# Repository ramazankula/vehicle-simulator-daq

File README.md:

# vehicle-simulator-daq
##Vehicle Simulator Data Acquisition Board

This project collects all simulator data and sends them to the simulation software using USB port.

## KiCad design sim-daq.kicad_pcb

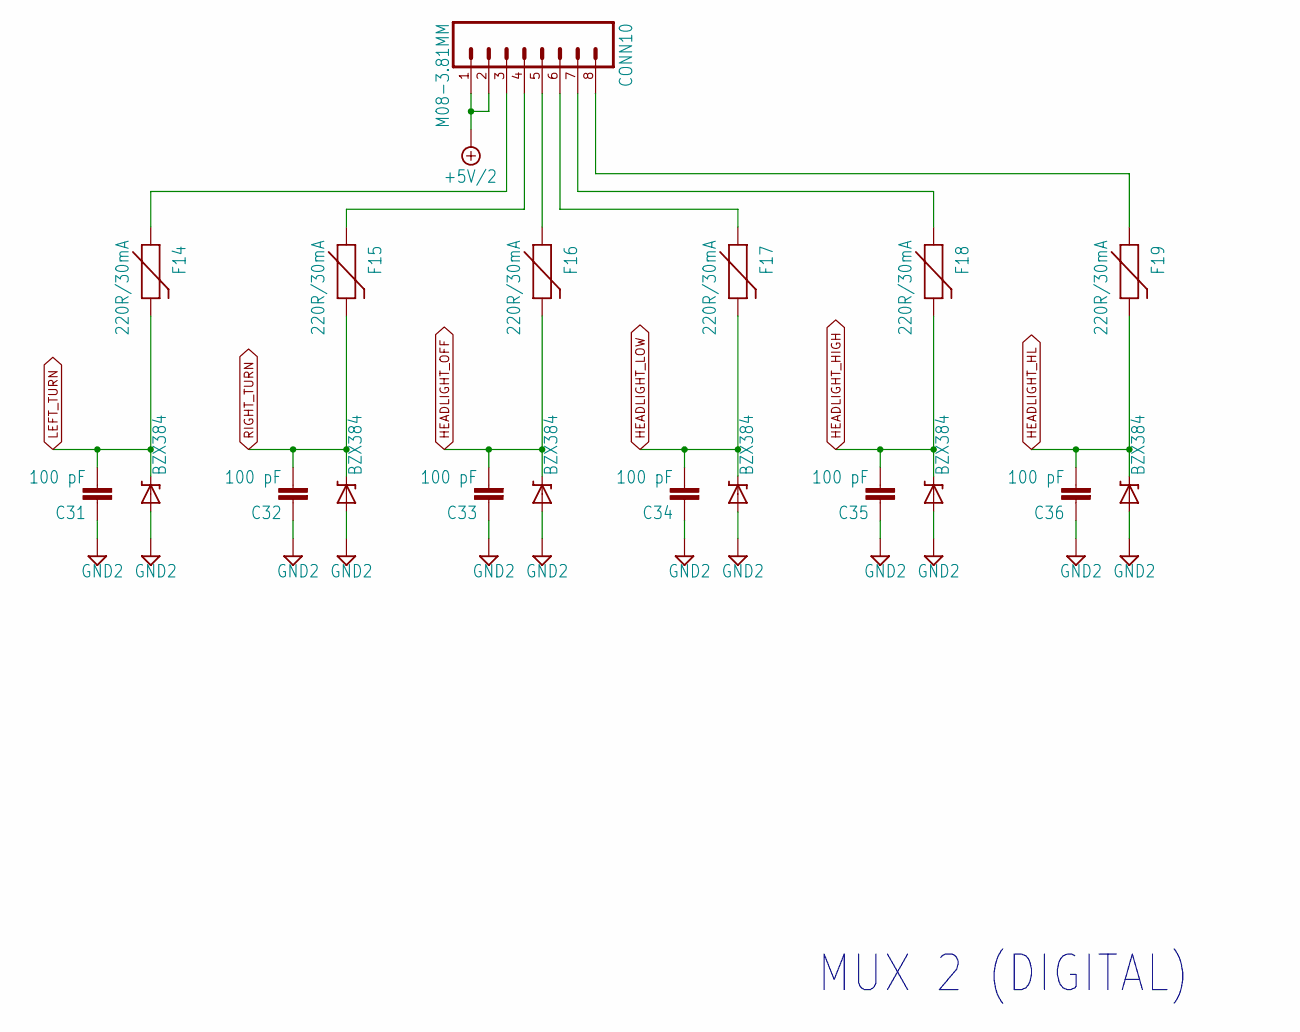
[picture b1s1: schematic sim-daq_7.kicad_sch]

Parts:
C31, C32, C33, C34, C35, C36: 100 pF; C0805; PARTNO *
CONN10: M08-3.81MM; M08-3.81; PARTNO *
D33, D34, D35, D36, D37, D38: BZX384; SOD-323; PARTNO *
F14, F15, F16, F17, F18, F19: 220R/30mA; 0603; PARTNO *

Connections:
+5V/2: CONN10.1, CONN10.2; also elsewhere on the board
GND2: C31.1, C32.1, C33.1, C34.1, C35.1, C36.1, D33.A, D34.A, D35.A, D36.A, D37.A, D38.A; also elsewhere on the board
HEADLIGHT_HIGH: C35.2, D37.C, F18.2; also elsewhere on the board
HEADLIGHT_HL: C36.2, D38.C, F19.2; also elsewhere on the board
HEADLIGHT_LOW: C34.2, D36.C, F17.2; also elsewhere on the board
HEADLIGHT_OFF: C33.2, D35.C, F16.2; also elsewhere on the board
LEFT_TURN: C31.2, D33.C, F14.2; also elsewhere on the board
unnamed: CONN10.3, F14.1
unnamed: CONN10.4, F15.1
unnamed: CONN10.5, F16.1
unnamed: CONN10.6, F17.1
unnamed: CONN10.7, F18.1
unnamed: CONN10.8, F19.1
RIGHT_TURN: C32.2, D34.C, F15.2; also elsewhere on the board

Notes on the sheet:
MUX 2 (DIGITAL)

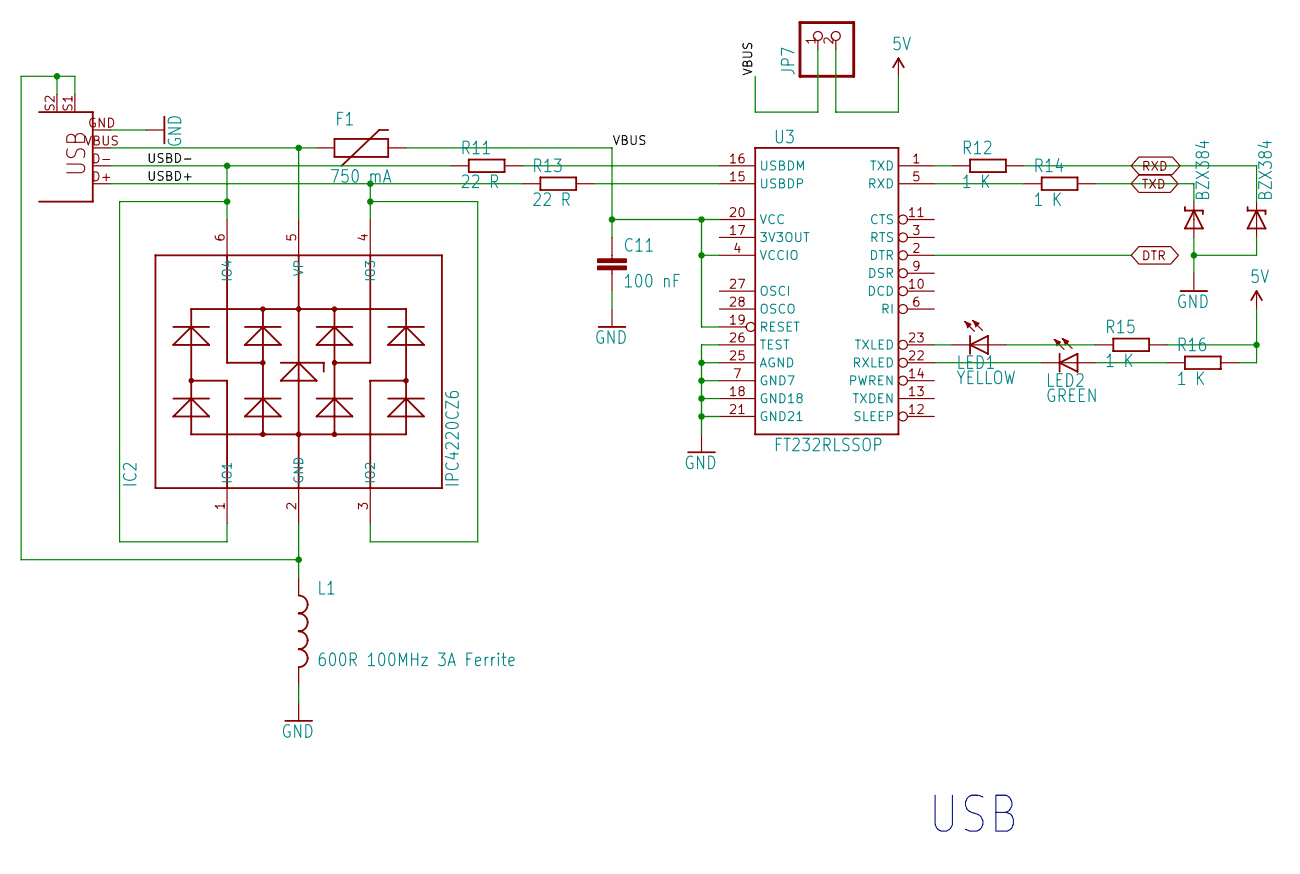
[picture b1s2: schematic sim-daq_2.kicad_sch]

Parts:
C11: 100 nF; C0805; PARTNO *
CONN2: USB+SHIELD; USB-B-PTH; PARTNO *
D14, D15: BZX384; SOD-323; PARTNO *
F1: 750 mA; PTC-1206-WIDE; PARTNO *
IC2: IPC4220CZ6; TSOP-6; PARTNO *
JP7: PINHD-1X2; 1X02; PARTNO *
L1: 600R 100MHz 3A Ferrite; 1210; PARTNO *
LED1: YELLOW; CHIPLED_0805; PARTNO *
LED2: GREEN; CHIPLED_0805; PARTNO *
R11, R13: 22 R; R0805; PARTNO *
R12, R14, R15, R16: 1 K; R0805; PARTNO *
U3: FT232RLSSOP; SSOP28DB; PARTNO *

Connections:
5V: JP7.2, R15.2, R16.2; also elsewhere on the board
/sim-daq_2/USBD+: CONN2.D+, IC2.3 (IO2), IC2.4 (IO3), R13.1
/sim-daq_2/USBD-: CONN2.D-, IC2.1 (IO1), IC2.6 (IO4), R11.1
/sim-daq_2/VBUS: C11.1, F1.2, JP7.1, U3.4 (VCCIO), U3.19 (RESET), U3.20 (VCC)
DTR: U3.2 (DTR); also elsewhere on the board
GND: C11.2, CONN2.GND, D14.A, D15.A, L1.2, U3.7 (GND7), U3.18 (GND18), U3.21 (GND21), U3.25 (AGND), U3.26 (TEST); also elsewhere on the board
unnamed: CONN2.S1, CONN2.S2, IC2.2 (GND), L1.1
unnamed: CONN2.VBUS, F1.1, IC2.5 (VP)
unnamed: LED1.A, R15.1
unnamed: LED2.A, R16.1
unnamed: R14.1, U3.5 (RXD)
unnamed: LED2.C, U3.22 (RXLED)
unnamed: R12.1, U3.1 (TXD)
unnamed: LED1.C, U3.23 (TXLED)
unnamed: R11.2, U3.16 (USBDM)
unnamed: R13.2, U3.15 (USBDP)
RXD: D15.C, R12.2; also elsewhere on the board
TXD: D14.C, R14.2; also elsewhere on the board

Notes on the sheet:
USB

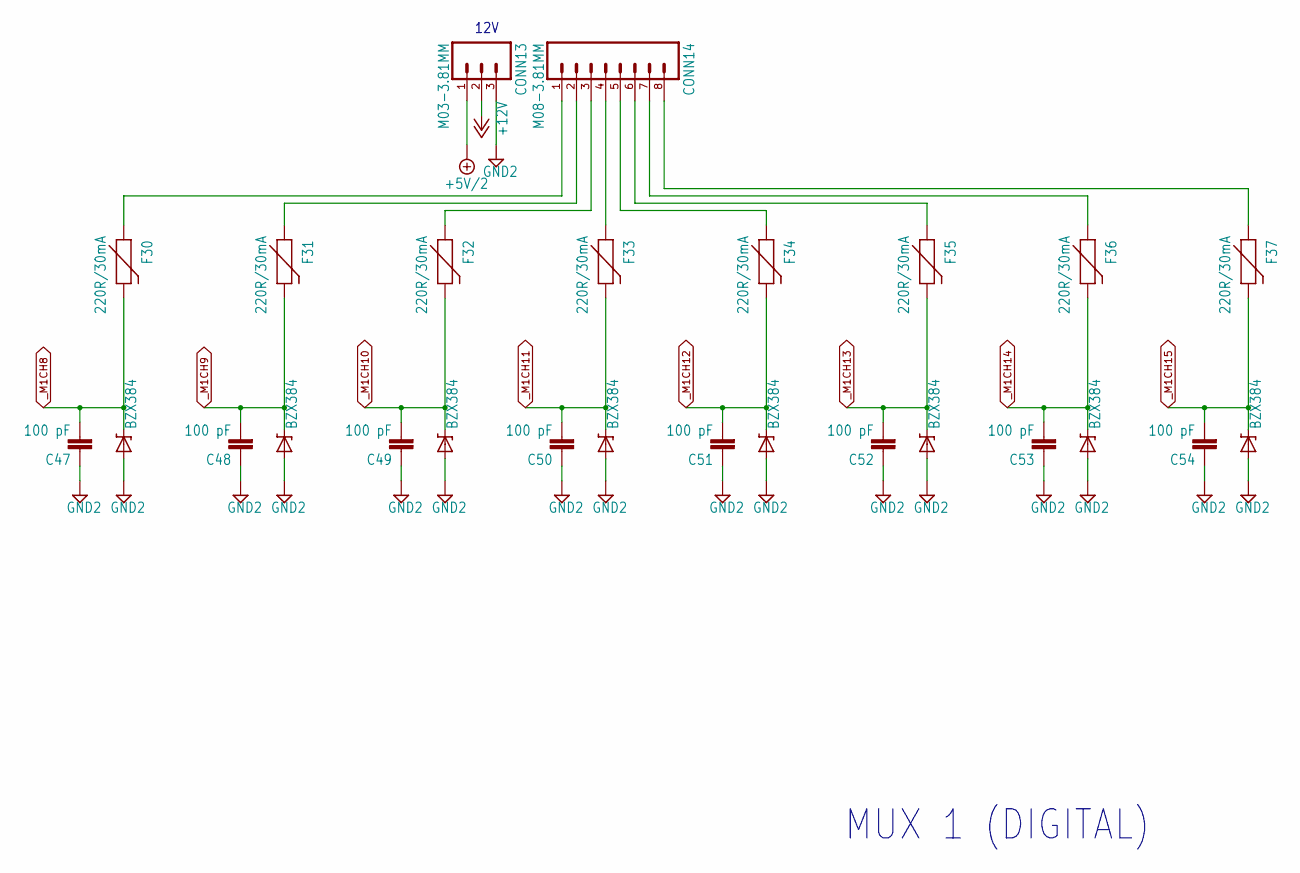
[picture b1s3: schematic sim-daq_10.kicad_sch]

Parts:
C47, C48, C49, C50, C51, C52, C53, C54: 100 pF; C0805; PARTNO *
CONN13: M03-3.81MM; M03-3.81; PARTNO *
CONN14: M08-3.81MM; M08-3.81; PARTNO *
D49, D50, D51, D52, D53, D54, D55, D56: BZX384; SOD-323; PARTNO *
F30, F31, F32, F33, F34, F35, F36, F37: 220R/30mA; 0603; PARTNO *

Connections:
+5V/2: CONN13.1; also elsewhere on the board
+12V: CONN13.2; also elsewhere on the board
GND2: C47.1, C48.1, C49.1, C50.1, C51.1, C52.1, C53.1, C54.1, CONN13.3, D49.A, D50.A, D51.A, D52.A, D53.A, D54.A, D55.A, D56.A; also elsewhere on the board
unnamed: CONN14.1, F30.1
unnamed: CONN14.2, F31.1
unnamed: CONN14.3, F32.1
unnamed: CONN14.4, F33.1
unnamed: CONN14.5, F34.1
unnamed: CONN14.6, F35.1
unnamed: CONN14.7, F36.1
unnamed: CONN14.8, F37.1
_M1CH8: C47.2, D49.C, F30.2; also elsewhere on the board
_M1CH9: C48.2, D50.C, F31.2; also elsewhere on the board
_M1CH10: C49.2, D51.C, F32.2; also elsewhere on the board
_M1CH11: C50.2, D52.C, F33.2; also elsewhere on the board
_M1CH12: C51.2, D53.C, F34.2; also elsewhere on the board
_M1CH13: C52.2, D54.C, F35.2; also elsewhere on the board
_M1CH14: C53.2, D55.C, F36.2; also elsewhere on the board
_M1CH15: C54.2, D56.C, F37.2; also elsewhere on the board

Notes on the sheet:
12V
MUX 1 (DIGITAL)

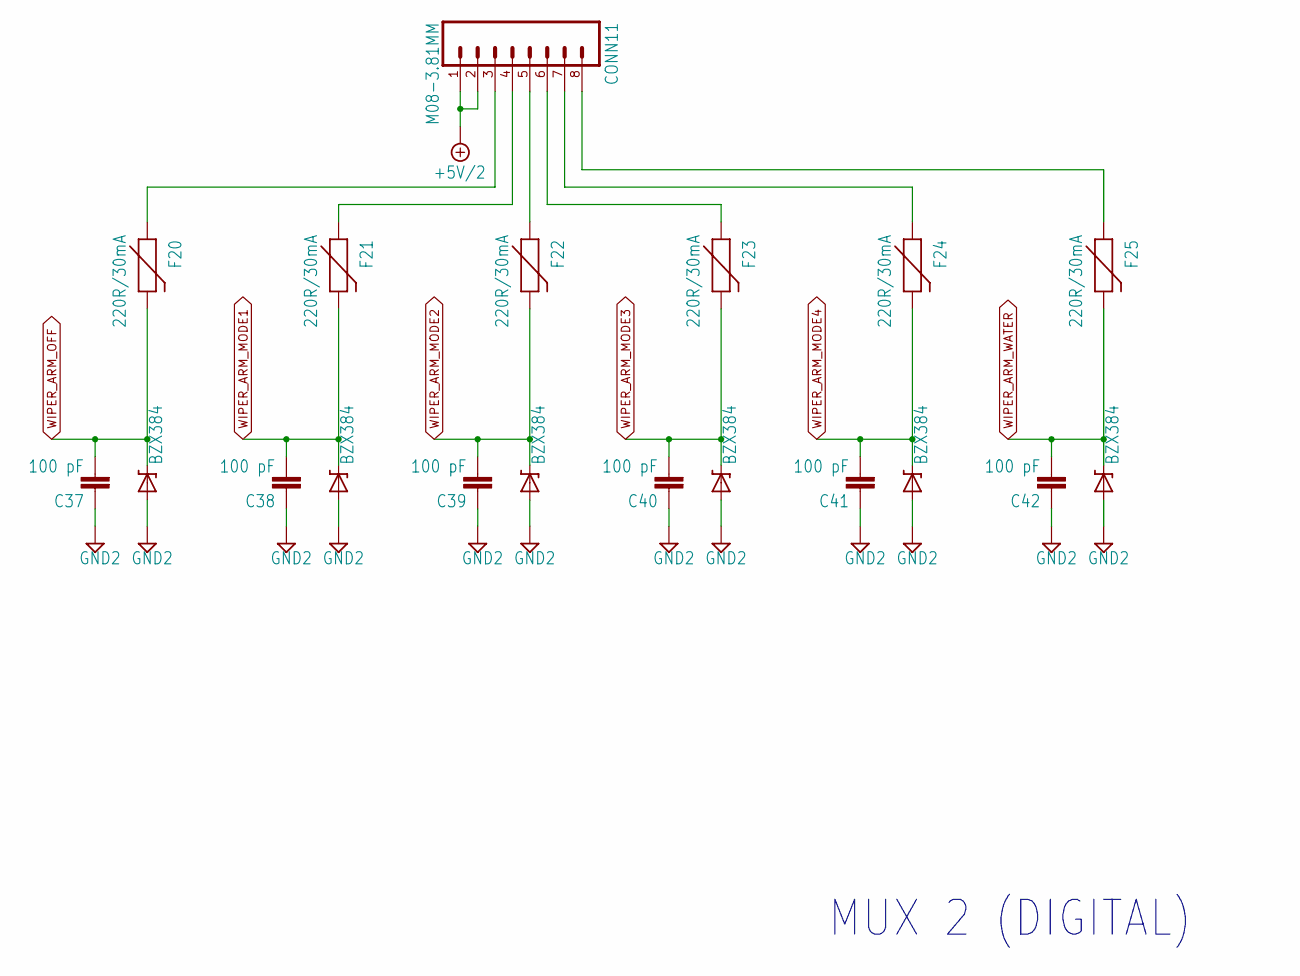
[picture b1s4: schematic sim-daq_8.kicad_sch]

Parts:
C37, C38, C39, C40, C41, C42: 100 pF; C0805; PARTNO *
CONN11: M08-3.81MM; M08-3.81; PARTNO *
D39, D40, D41, D42, D43, D44: BZX384; SOD-323; PARTNO *
F20, F21, F22, F23, F24, F25: 220R/30mA; 0603; PARTNO *

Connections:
+5V/2: CONN11.1, CONN11.2; also elsewhere on the board
GND2: C37.1, C38.1, C39.1, C40.1, C41.1, C42.1, D39.A, D40.A, D41.A, D42.A, D43.A, D44.A; also elsewhere on the board
unnamed: CONN11.3, F20.1
unnamed: CONN11.4, F21.1
unnamed: CONN11.5, F22.1
unnamed: CONN11.6, F23.1
unnamed: CONN11.7, F24.1
unnamed: CONN11.8, F25.1
WIPER_ARM_MODE1: C38.2, D40.C, F21.2; also elsewhere on the board
WIPER_ARM_MODE2: C39.2, D41.C, F22.2; also elsewhere on the board
WIPER_ARM_MODE3: C40.2, D42.C, F23.2; also elsewhere on the board
WIPER_ARM_MODE4: C41.2, D43.C, F24.2; also elsewhere on the board
WIPER_ARM_OFF: C37.2, D39.C, F20.2; also elsewhere on the board
WIPER_ARM_WATER: C42.2, D44.C, F25.2; also elsewhere on the board

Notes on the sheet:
MUX 2 (DIGITAL)

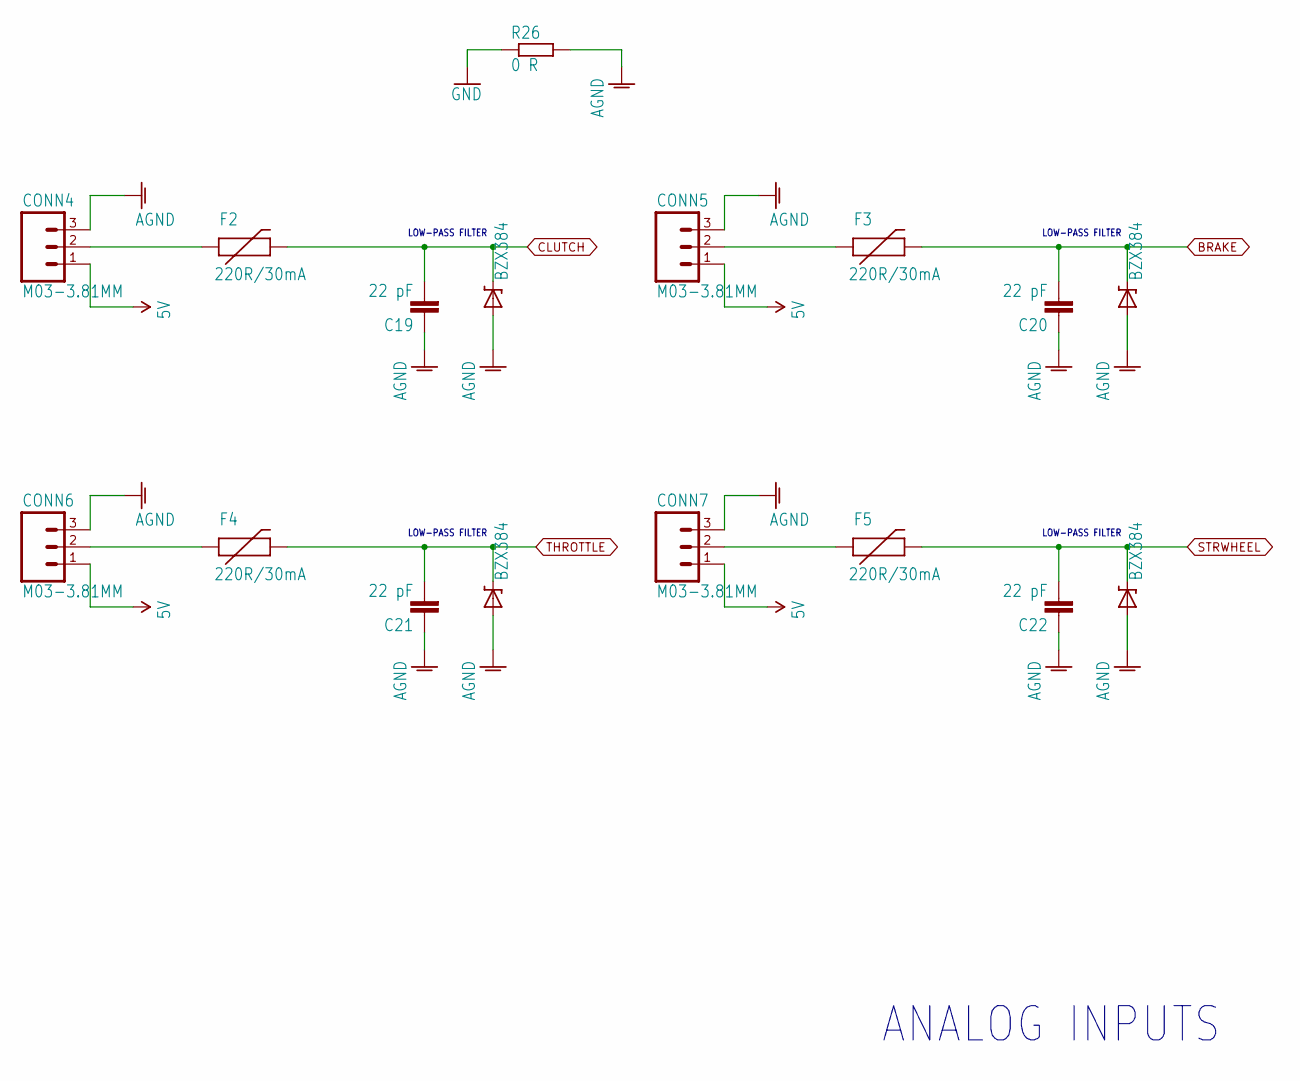
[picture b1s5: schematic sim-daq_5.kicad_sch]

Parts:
C19, C20, C21, C22: 22 pF; C0805; PARTNO *
CONN4, CONN5, CONN6, CONN7: M03-3.81MM; M03-3.81; PARTNO *
D21, D22, D23, D24: BZX384; SOD-323; PARTNO *
F2, F3, F4, F5: 220R/30mA; 0603; PARTNO *
R26: 0 R; R0805; PARTNO *

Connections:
5V: CONN4.1, CONN5.1, CONN6.1, CONN7.1; also elsewhere on the board
AGND: C19.1, C20.1, C21.1, C22.1, CONN4.3, CONN5.3, CONN6.3, CONN7.3, D21.A, D22.A, D23.A, D24.A, R26.2; also elsewhere on the board
BRAKE: C20.2, D22.C, F3.2; also elsewhere on the board
CLUTCH: C19.2, D21.C, F2.2; also elsewhere on the board
GND: R26.1; also elsewhere on the board
unnamed: CONN4.2, F2.1
unnamed: CONN5.2, F3.1
unnamed: CONN6.2, F4.1
unnamed: CONN7.2, F5.1
STRWHEEL: C22.2, D24.C, F5.2; also elsewhere on the board
THROTTLE: C21.2, D23.C, F4.2; also elsewhere on the board

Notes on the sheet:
LOW-PASS FILTER
ANALOG INPUTS

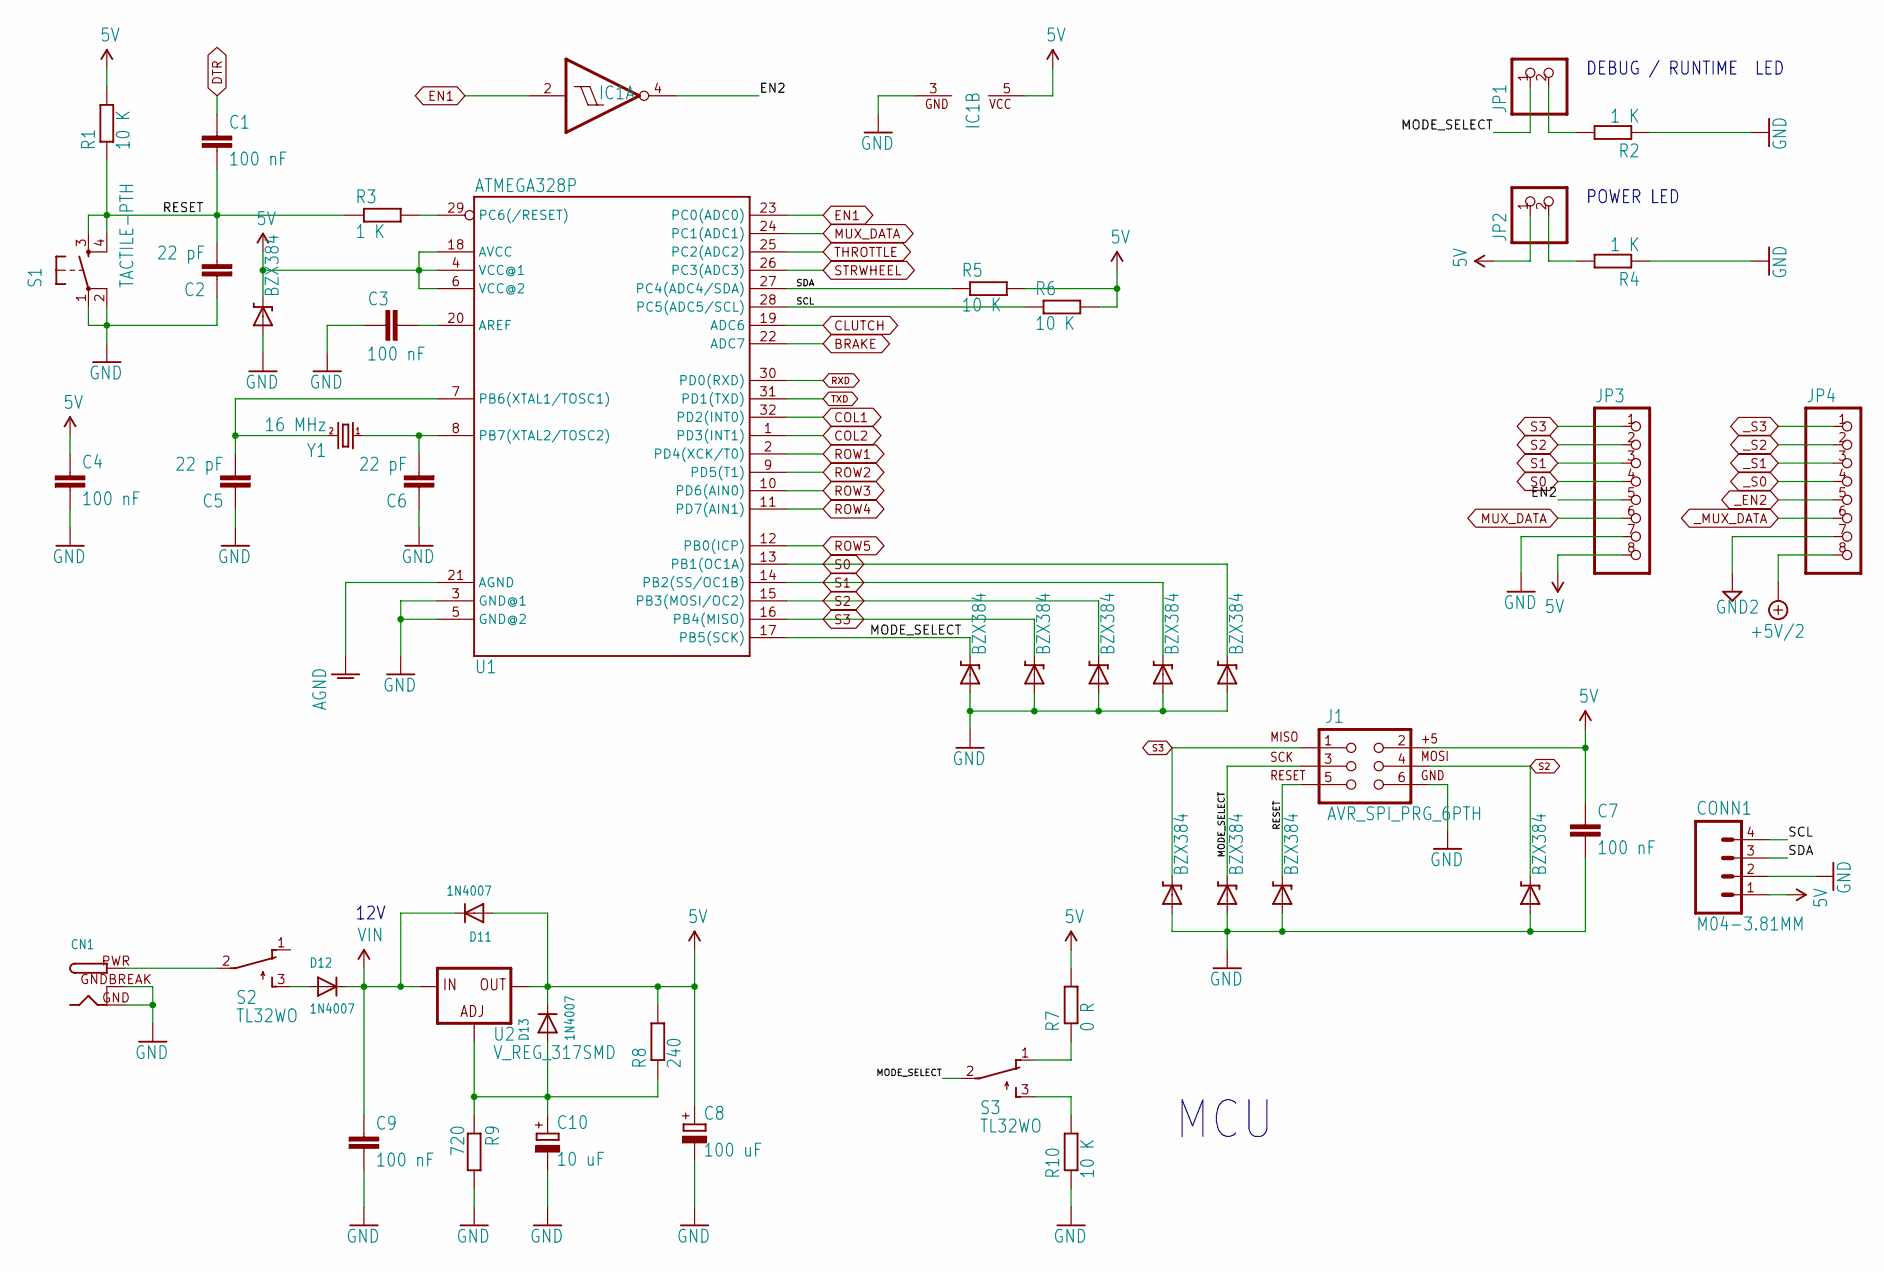
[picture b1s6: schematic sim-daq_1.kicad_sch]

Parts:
C1, C3, C4, C7, C9: 100 nF; C0805; PARTNO *
C2, C5, C6: 22 pF; C0805; PARTNO *
C8: 100 uF; PANASONIC_F; PARTNO *
C10: 10 uF; PANASONIC_C; PARTNO *
CN1: DCBARRELPTH; DCJACK_2MM_PTH
CONN1: M04-3.81MM; M04-3.81; PARTNO *
D1, D2, D3, D4, D5, D6, D7, D8, D9, D10: BZX384; SOD-323; PARTNO *
D11, D12, D13: 1N4007; SMADIODE; PARTNO *
IC1: 741G14DCK; SC70-5; PARTNO *
J1: AVR_SPI_PRG_6PTH; 2X3; PARTNO *
JP1, JP2: PINHD-1X2; 1X02; PARTNO *
JP3, JP4: PINHD-1X8; 1X08; PARTNO *
R1, R5, R6, R10: 10 K; R0805; PARTNO *
R2, R3, R4: 1 K; R0805; PARTNO *
R7: 0 R; R0805; PARTNO *
R8: 240; R0805; PARTNO *
R9: 720; R0805; PARTNO *
S1: TACTILE-PTH; PARTNO *
S2, S3: TL32WO; TL3XWO; PARTNO *
U1: ATMEGA328P; TQFP32-08; PARTNO *
U2: V_REG_317SMD; SOT223; PARTNO *
Y1: 16 MHz; HC49UP; PARTNO *

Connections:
5V: C4.1, C7.1, C8.+, CONN1.1, D1.C, D11.A, D13.C, IC1.5 (VCC), J1.2, JP2.1, JP3.8, R1.2, R5.2, R6.2, R7.2, R8.2, U1.4 (VCC@1), U1.6 (VCC@2), U1.18 (AVCC), U2.2 (OUT), U2.4 (OUT); also elsewhere on the board
+5V/2: JP4.8; also elsewhere on the board
/sim-daq_1/EN2: IC1.4 (O), JP3.5
/sim-daq_1/MODE_SELECT: D2.C, D8.C, J1.3, JP1.1, S3.2, U1.17 (PB5(SCK))
/sim-daq_1/RESET: C1.2, C2.2, D9.C, J1.5, R1.1, R3.1, S1.3, S1.4
/sim-daq_1/SCL: CONN1.4, R6.1, U1.28 (PC5(ADC5/SCL))
/sim-daq_1/SDA: CONN1.3, R5.1, U1.27 (PC4(ADC4/SDA))
AGND: U1.21 (AGND); also elsewhere on the board
BRAKE: U1.22 (ADC7); also elsewhere on the board
CLUTCH: U1.19 (ADC6); also elsewhere on the board
COL1: U1.32 (PD2(INT0)); also elsewhere on the board
COL2: U1.1 (PD3(INT1)); also elsewhere on the board
DTR: C1.1; also elsewhere on the board
EN1: IC1.2 (I), U1.23 (PC0(ADC0)); also elsewhere on the board
GND: C2.1, C3.1, C4.2, C5.1, C6.1, C7.2, C8.-, C9.2, C10.-, CN1.GND, CN1.GNDBREAK, CONN1.2, D1.A, D2.A, D3.A, D4.A, D5.A, D6.A, D7.A, D8.A, D9.A, D10.A, IC1.3 (GND), J1.6, JP3.7, R2.1, R4.1, R9.2, R10.1, S1.1, S1.2, U1.3 (GND@1), U1.5 (GND@2); also elsewhere on the board
GND2: JP4.7; also elsewhere on the board
MUX_DATA: JP3.6, U1.24 (PC1(ADC1)); also elsewhere on the board
unnamed: JP1.2, R2.2
unnamed: JP2.2, R4.2
unnamed: CN1.PWR, S2.2
unnamed: D12.A, S2.3 (S)
unnamed: R7.1, S3.1 (O)
unnamed: R10.2, S3.3 (S)
unnamed: C3.2, U1.20 (AREF)
unnamed: C5.2, U1.7 (PB6(XTAL1/TOSC1)), Y1.2
unnamed: C6.2, U1.8 (PB7(XTAL2/TOSC2)), Y1.1
unnamed: R3.2, U1.29 (PC6(/RESET))
unnamed: C10.+, D13.A, R8.1, R9.1, U2.1 (ADJ)
ROW1: U1.2 (PD4(XCK/T0)); also elsewhere on the board
ROW2: U1.9 (PD5(T1)); also elsewhere on the board
ROW3: U1.10 (PD6(AIN0)); also elsewhere on the board
ROW4: U1.11 (PD7(AIN1)); also elsewhere on the board
ROW5: U1.12 (PB0(ICP)); also elsewhere on the board
RXD: U1.30 (PD0(RXD)); also elsewhere on the board
S0: D6.C, JP3.4, U1.13 (PB1(OC1A)); also elsewhere on the board
S1: D5.C, JP3.3, U1.14 (PB2(SS/OC1B)); also elsewhere on the board
S2: D4.C, D10.C, J1.4, JP3.2, U1.15 (PB3(MOSI/OC2)); also elsewhere on the board
S3: D3.C, D7.C, J1.1, JP3.1, U1.16 (PB4(MISO)); also elsewhere on the board
STRWHEEL: U1.26 (PC3(ADC3)); also elsewhere on the board
THROTTLE: U1.25 (PC2(ADC2)); also elsewhere on the board
TXD: U1.31 (PD1(TXD)); also elsewhere on the board
VIN: C9.1, D11.C, D12.C, U2.3 (IN); also elsewhere on the board
_EN2: JP4.5; also elsewhere on the board
_MUX_DATA: JP4.6; also elsewhere on the board
_S0: JP4.4; also elsewhere on the board
_S1: JP4.3; also elsewhere on the board
_S2: JP4.2; also elsewhere on the board
_S3: JP4.1; also elsewhere on the board

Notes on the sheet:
MCU
POWER LED
12V
DEBUG / RUNTIME LED

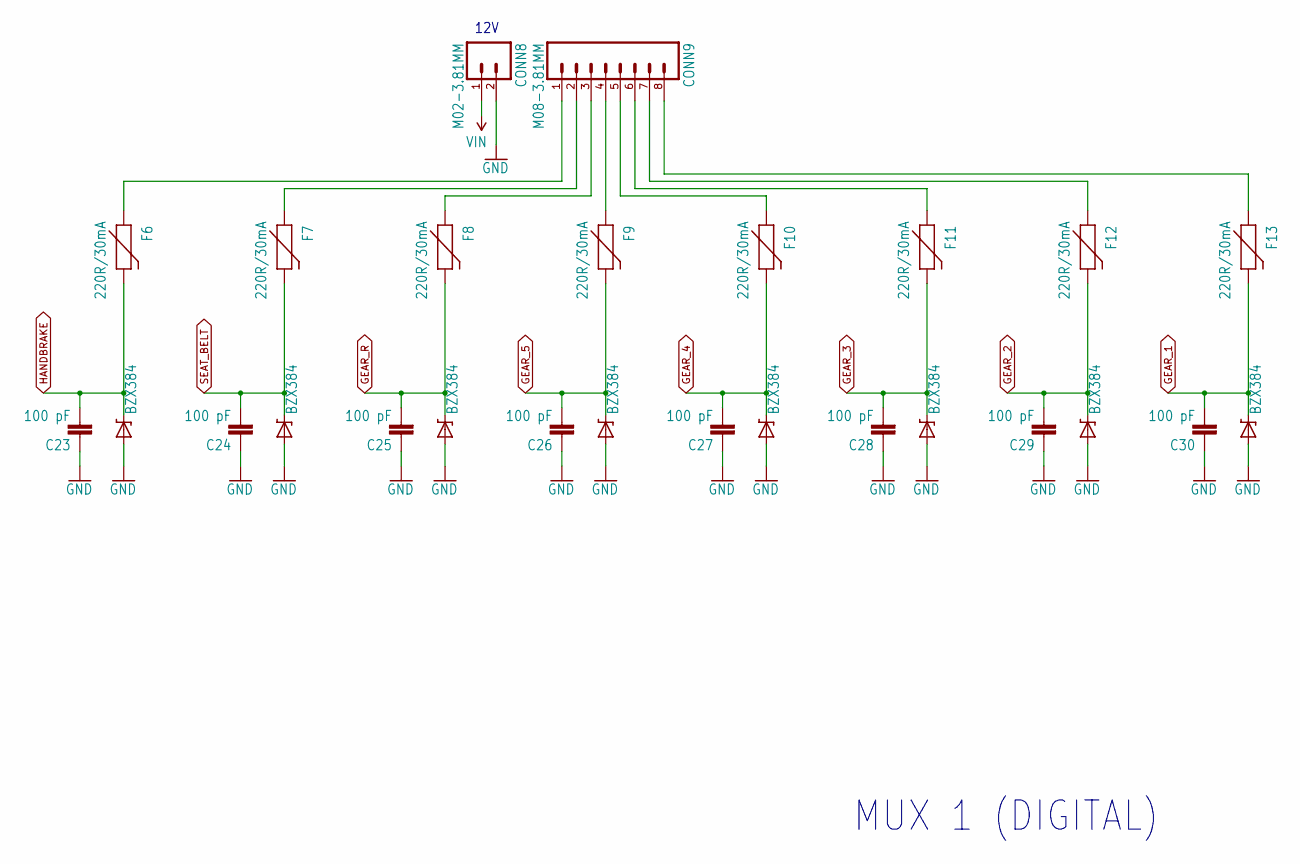
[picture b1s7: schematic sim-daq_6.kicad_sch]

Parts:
C23, C24, C25, C26, C27, C28, C29, C30: 100 pF; C0805; PARTNO *
CONN8: M02-3.81MM; PARTNO *
CONN9: M08-3.81MM; M08-3.81; PARTNO *
D25, D26, D27, D28, D29, D30, D31, D32: BZX384; SOD-323; PARTNO *
F6, F7, F8, F9, F10, F11, F12, F13: 220R/30mA; 0603; PARTNO *

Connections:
GEAR_1: C30.2, D32.C, F13.2; also elsewhere on the board
GEAR_2: C29.2, D31.C, F12.2; also elsewhere on the board
GEAR_3: C28.2, D30.C, F11.2; also elsewhere on the board
GEAR_4: C27.2, D29.C, F10.2; also elsewhere on the board
GEAR_5: C26.2, D28.C, F9.2; also elsewhere on the board
GEAR_R: C25.2, D27.C, F8.2; also elsewhere on the board
GND: C23.1, C24.1, C25.1, C26.1, C27.1, C28.1, C29.1, C30.1, CONN8.2, D25.A, D26.A, D27.A, D28.A, D29.A, D30.A, D31.A, D32.A; also elsewhere on the board
HANDBRAKE: C23.2, D25.C, F6.2; also elsewhere on the board
unnamed: CONN9.1, F6.1
unnamed: CONN9.2, F7.1
unnamed: CONN9.3, F8.1
unnamed: CONN9.4, F9.1
unnamed: CONN9.5, F10.1
unnamed: CONN9.6, F11.1
unnamed: CONN9.7, F12.1
unnamed: CONN9.8, F13.1
SEAT_BELT: C24.2, D26.C, F7.2; also elsewhere on the board
VIN: CONN8.1; also elsewhere on the board

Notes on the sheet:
MUX 1 (DIGITAL)
12V

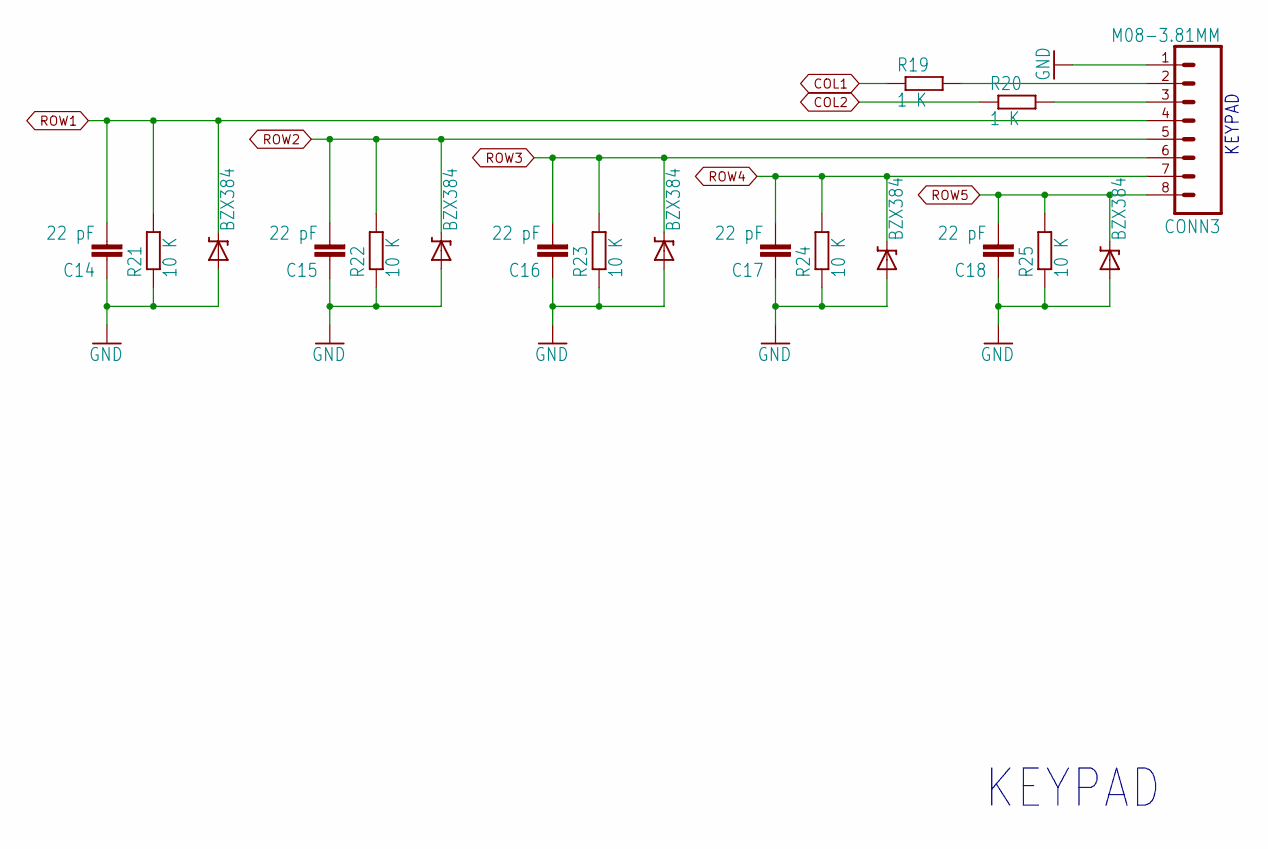
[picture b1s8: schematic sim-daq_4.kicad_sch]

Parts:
C14, C15, C16, C17, C18: 22 pF; C0805; PARTNO *
CONN3: M08-3.81MM; M08-3.81; PARTNO *
D16, D17, D18, D19, D20: BZX384; SOD-323; PARTNO *
R19, R20: 1 K; R0805; PARTNO *
R21, R22, R23, R24, R25: 10 K; R0805; PARTNO *

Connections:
COL1: R19.1; also elsewhere on the board
COL2: R20.1; also elsewhere on the board
GND: C14.1, C15.1, C16.1, C17.1, C18.1, CONN3.1, D16.A, D17.A, D18.A, D19.A, D20.A, R21.1, R22.1, R23.1, R24.1, R25.1; also elsewhere on the board
unnamed: CONN3.2, R19.2
unnamed: CONN3.3, R20.2
ROW1: C14.2, CONN3.4, D16.C, R21.2; also elsewhere on the board
ROW2: C15.2, CONN3.5, D17.C, R22.2; also elsewhere on the board
ROW3: C16.2, CONN3.6, D18.C, R23.2; also elsewhere on the board
ROW4: C17.2, CONN3.7, D19.C, R24.2; also elsewhere on the board
ROW5: C18.2, CONN3.8, D20.C, R25.2; also elsewhere on the board

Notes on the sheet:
KEYPAD

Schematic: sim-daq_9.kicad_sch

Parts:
C43, C44, C45, C46: 100 pF; C0805; PARTNO *
CONN12: M08-3.81MM; M08-3.81; PARTNO *
D45, D46, D47, D48: BZX384; SOD-323; PARTNO *
F26, F27, F28, F29: 220R/30mA; 0603; PARTNO *

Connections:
+5V/2: CONN12.1, CONN12.3; also elsewhere on the board
GND2: C43.1, C44.1, C45.1, C46.1, CONN12.2, CONN12.4, D45.A, D46.A, D47.A, D48.A; also elsewhere on the board
HORN: C46.2, D48.C, F29.2; also elsewhere on the board
IGNITION_1: C43.2, D45.C, F26.2; also elsewhere on the board
IGNITION_2: C44.2, D46.C, F27.2; also elsewhere on the board
IGNITION_3: C45.2, D47.C, F28.2; also elsewhere on the board
unnamed: CONN12.5, F26.1
unnamed: CONN12.6, F27.1
unnamed: CONN12.7, F28.1
unnamed: CONN12.8, F29.1

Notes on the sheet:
MUX 2 (DIGITAL)

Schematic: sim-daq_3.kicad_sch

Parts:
C12, C13: 100 nF; C0805; PARTNO *
IC3, IC4: MUX-74HC4067SMD; SSOP24; PARTNO *
JP5, JP6: PINHD-1X9; 1X09; PARTNO *
R17, R18: 10 K; R0805; PARTNO *

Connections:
5V: C12.1, IC3.24 (VCC); also elsewhere on the board
+5V/2: C13.1, IC4.24 (VCC); also elsewhere on the board
+12V: JP6.9; also elsewhere on the board
/sim-daq_3/M1CH8: IC3.23 (CHAN8), JP5.1
/sim-daq_3/M1CH9: IC3.22 (CHAN9), JP5.2
/sim-daq_3/M1CH10: IC3.21 (CHAN10), JP5.3
/sim-daq_3/M1CH11: IC3.20 (CHAN11), JP5.4
/sim-daq_3/M1CH12: IC3.19 (CHAN12), JP5.5
/sim-daq_3/M1CH13: IC3.18 (CHAN13), JP5.6
/sim-daq_3/M1CH14: IC3.17 (CHAN14), JP5.7
/sim-daq_3/M1CH15: IC3.16 (CHAN15), JP5.8
EN1: IC3.15 (EN), R17.2; also elsewhere on the board
GEAR_1: IC3.9 (CHAN0); also elsewhere on the board
GEAR_2: IC3.8 (CHAN1); also elsewhere on the board
GEAR_3: IC3.7 (CHAN2); also elsewhere on the board
GEAR_4: IC3.6 (CHAN3); also elsewhere on the board
GEAR_5: IC3.5 (CHAN4); also elsewhere on the board
GEAR_R: IC3.4 (CHAN5); also elsewhere on the board
GND: C12.2, IC3.12 (GND), R17.1; also elsewhere on the board
GND2: C13.2, IC4.12 (GND), R18.1; also elsewhere on the board
HANDBRAKE: IC3.2 (CHAN7); also elsewhere on the board
HEADLIGHT_HIGH: IC4.5 (CHAN4); also elsewhere on the board
HEADLIGHT_HL: IC4.4 (CHAN5); also elsewhere on the board
HEADLIGHT_LOW: IC4.6 (CHAN3); also elsewhere on the board
HEADLIGHT_OFF: IC4.7 (CHAN2); also elsewhere on the board
HORN: IC4.16 (CHAN15); also elsewhere on the board
IGNITION_1: IC4.19 (CHAN12); also elsewhere on the board
IGNITION_2: IC4.18 (CHAN13); also elsewhere on the board
IGNITION_3: IC4.17 (CHAN14); also elsewhere on the board
LEFT_TURN: IC4.9 (CHAN0); also elsewhere on the board
MUX_DATA: IC3.1 (COM); also elsewhere on the board
RIGHT_TURN: IC4.8 (CHAN1); also elsewhere on the board
S0: IC3.10 (S0); also elsewhere on the board
S1: IC3.11 (S1); also elsewhere on the board
S2: IC3.14 (S2); also elsewhere on the board
S3: IC3.13 (S3); also elsewhere on the board
SEAT_BELT: IC3.3 (CHAN6); also elsewhere on the board
VIN: JP5.9; also elsewhere on the board
WIPER_ARM_MODE1: IC4.2 (CHAN7); also elsewhere on the board
WIPER_ARM_MODE2: IC4.23 (CHAN8); also elsewhere on the board
WIPER_ARM_MODE3: IC4.22 (CHAN9); also elsewhere on the board
WIPER_ARM_MODE4: IC4.21 (CHAN10); also elsewhere on the board
WIPER_ARM_OFF: IC4.3 (CHAN6); also elsewhere on the board
WIPER_ARM_WATER: IC4.20 (CHAN11); also elsewhere on the board
_EN2: IC4.15 (EN), R18.2; also elsewhere on the board
_M1CH8: JP6.1; also elsewhere on the board
_M1CH9: JP6.2; also elsewhere on the board
_M1CH10: JP6.3; also elsewhere on the board
_M1CH11: JP6.4; also elsewhere on the board
_M1CH12: JP6.5; also elsewhere on the board
_M1CH13: JP6.6; also elsewhere on the board
_M1CH14: JP6.7; also elsewhere on the board
_M1CH15: JP6.8; also elsewhere on the board
_MUX_DATA: IC4.1 (COM); also elsewhere on the board
_S0: IC4.10 (S0); also elsewhere on the board
_S1: IC4.11 (S1); also elsewhere on the board
_S2: IC4.14 (S2); also elsewhere on the board
_S3: IC4.13 (S3); also elsewhere on the board

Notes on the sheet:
MUX

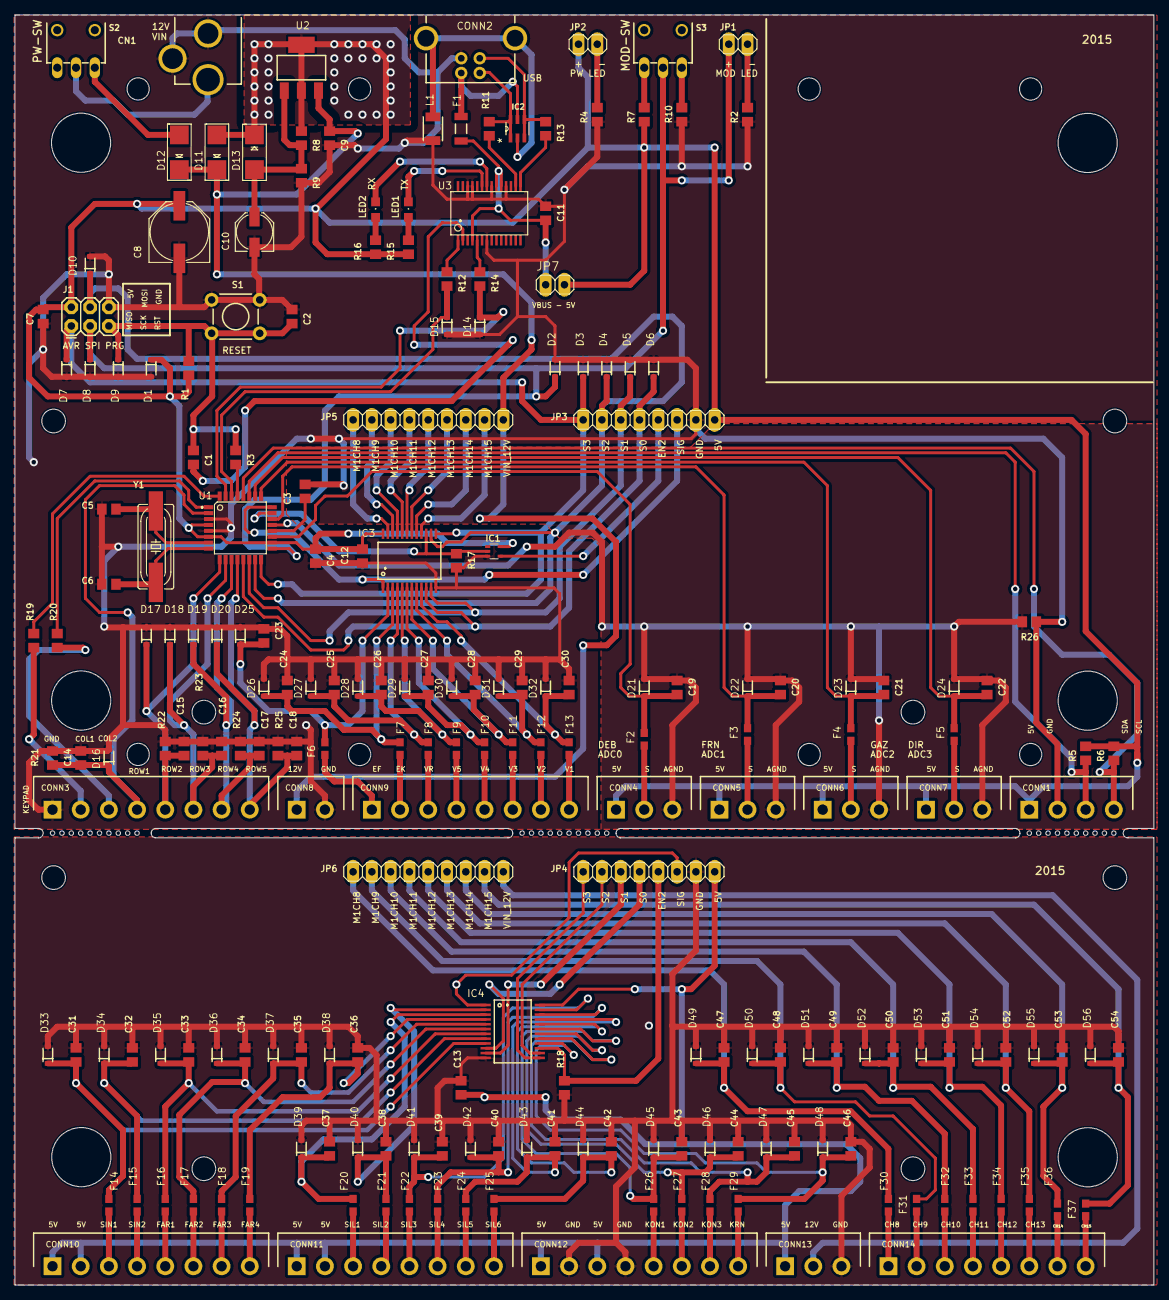
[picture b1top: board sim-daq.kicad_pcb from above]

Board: 2 copper layers, 154.0 x 171.7 mm, 262 parts (0 on the bottom side), 140 nets.

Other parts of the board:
@HOLE0, @HOLE1, @HOLE2, @HOLE3, @HOLE4, @HOLE5, @HOLE6, @HOLE7, @HOLE8, @HOLE9, @HOLE10, @HOLE11, @HOLE12, @HOLE13, @HOLE14, @HOLE15, @HOLE16, @HOLE17, @HOLE18, @HOLE19, @HOLE20, @HOLE21, @HOLE22, @HOLE23, @HOLE24, @HOLE25, @HOLE26, @HOLE27, @HOLE28, @HOLE29, @HOLE30, @HOLE31, @HOLE32, @HOLE33, @HOLE34, @HOLE35, @HOLE36, @HOLE37, @HOLE38, @HOLE39, @HOLE40, @HOLE41, @HOLE42, @HOLE43, @HOLE44, @HOLE45, @HOLE46, @HOLE47, @HOLE48, @HOLE49, @HOLE50, @HOLE51: (no value)
